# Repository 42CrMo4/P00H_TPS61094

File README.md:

# TPS61094

Eval board for TPS61094

## Goal

The goal of the project will be:
- [ ] **undefined** - not known what the project will bring 
- [ ] **learn** - personally learn something new, no usefull outcome expected
- [x] **prototype** - a working prototype or mvp
- [ ] **80-20-rule** - 80% outcome with 20% effort
- [ ] **Product** - lets see :wink:

## Description. 

| Font                                                                    | Back                                                                      |
|-------------------------------------------------------------------------|---------------------------------------------------------------------------|
|  |  |

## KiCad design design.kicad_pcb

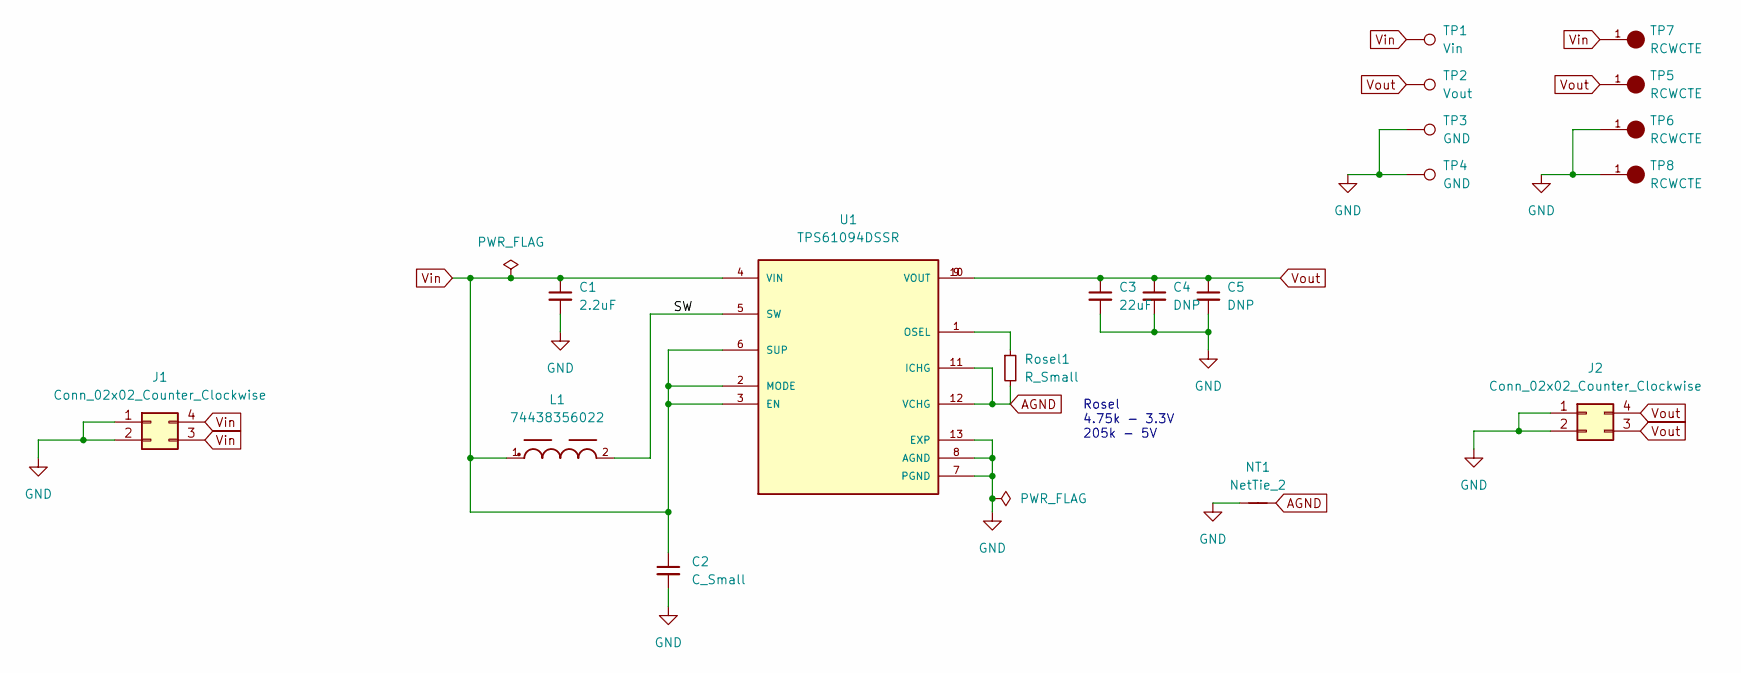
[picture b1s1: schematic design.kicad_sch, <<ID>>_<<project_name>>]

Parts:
C1: 2.2uF; C_0805_2012Metric
C2: C_Small; C_0805_2012Metric
C3: 22uF; C_0805_2012Metric
C4, C5: DNP; C_0805_2012Metric
J1, J2: Conn_02x02_Counter_Clockwise; PinHeader_2x02_P2.54mm_Vertical
L1: 74438356022; WE-MAPI_4020_WE-MAPI_4020
NT1: NetTie_2; NetTie-2_SMD_Pad0.5mm
Rosel1: R_Small; R_0805_2012Metric
TP1: Vin; TestPoint_Pad_D3.0mm
TP2: Vout; TestPoint_Pad_D3.0mm
TP3, TP4: GND; TestPoint_Pad_D3.0mm
TP5, TP6, TP7, TP8: RCWCTE; RCWCTE_TP420X150; PARTREV 1/06/14
U1: TPS61094DSSR; TPS61094DSSR_SON50P300X200X80-13N; PARTREV C

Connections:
/SW: L1.2, U1.5 (SW)
AGND: NT1.2, Rosel1.2, U1.11 (ICHG), U1.12 (VCHG)
GND: C1.2, C2.2, C3.2, C4.2, C5.2, J1.1, J1.2, J2.1, J2.2, NT1.1, TP3.1, TP4.1, TP6.1, TP8.1, U1.7 (PGND), U1.8 (AGND), U1.13 (EXP)
unnamed: Rosel1.1, U1.1 (OSEL)
Vin: C1.1, C2.1, J1.3, J1.4, L1.1, TP1.1, TP7.1, U1.2 (MODE), U1.3 (EN), U1.4 (VIN), U1.6 (SUP)
Vout: C3.1, C4.1, C5.1, J2.3, J2.4, TP2.1, TP5.1, U1.9 (VOUT), U1.10 (VOUT)

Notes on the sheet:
Rosel 4.75k - 3.3V 205k - 5V

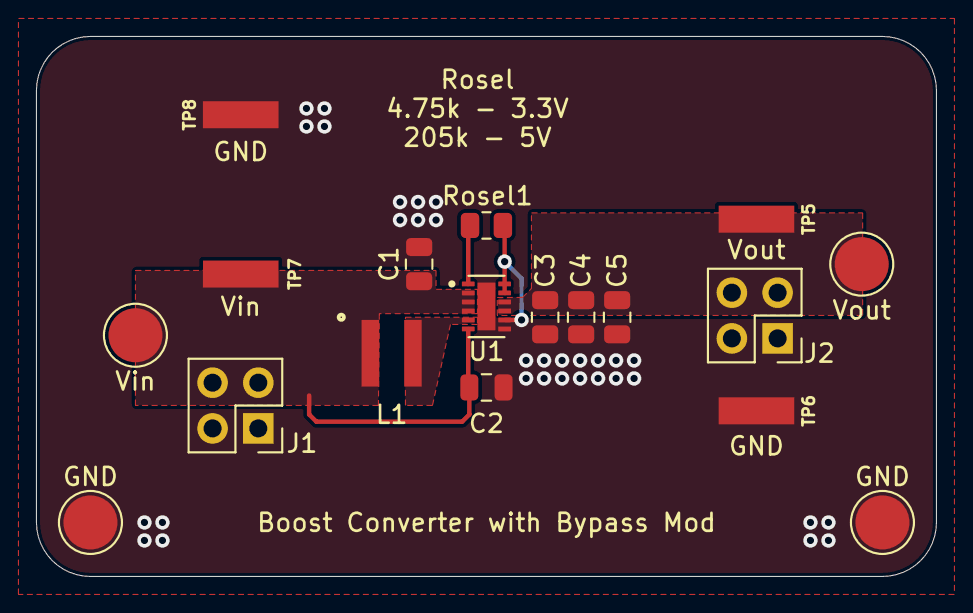
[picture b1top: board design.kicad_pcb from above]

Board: 2 copper layers, 50.0 x 30.0 mm, 19 parts (1 on the bottom side), 6 nets.

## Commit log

2025-01-26 DEL Template stuff
2025-01-26 Update Bom and PCB_top
2025-01-26 release notes and checklist
2025-01-26 Archive & Renew release docs
